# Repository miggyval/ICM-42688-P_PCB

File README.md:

This is a repository for the ICM-42688-P_PCB KiCAD project by Miguel Valencia

[Link to BOM](https://html-preview.github.io/?url=https://github.com/miggyval/ICM-42688-P_PCB/blob/main/bom/ibom.html)

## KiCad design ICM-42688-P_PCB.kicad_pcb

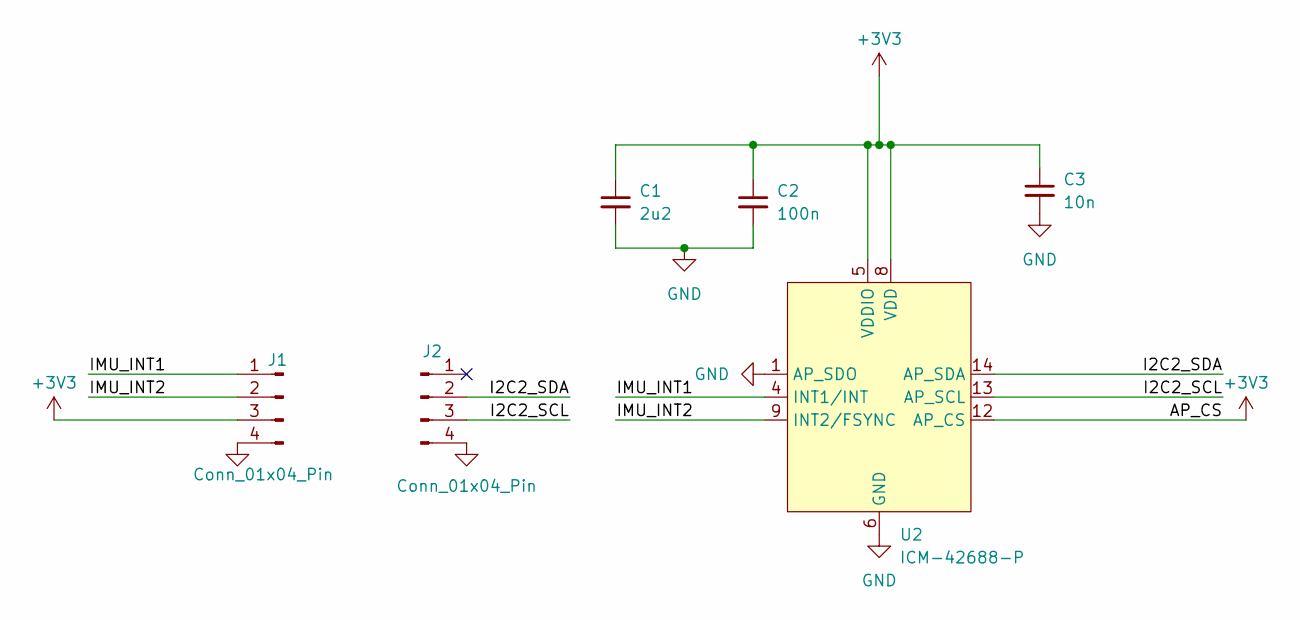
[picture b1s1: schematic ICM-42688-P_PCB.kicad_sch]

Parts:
C1: 2u2; C_1206_3216Metric_Pad1.33x1.80mm_HandSolder
C2: 100n; C_1206_3216Metric_Pad1.33x1.80mm_HandSolder
C3: 10n; C_1206_3216Metric_Pad1.33x1.80mm_HandSolder
J1, J2: Conn_01x04_Pin; PinHeader_1x04_P2.54mm_Vertical
U2: ICM-42688-P; LGA-14_3x2.5mm_P0.5mm_LayoutBorder3x4y_Keepout

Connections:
+3V3: C1.1, C2.1, C3.1, J1.3, U2.5 (VDDIO), U2.8 (VDD), U2.12 (AP_CS)
/I2C2_SCL: J2.3, U2.13 (AP_SCL)
/I2C2_SDA: J2.2, U2.14 (AP_SDA)
/IMU_INT1: J1.1, U2.4 (INT1/INT)
/IMU_INT2: J1.2, U2.9 (INT2/FSYNC)
GND: C1.2, C2.2, C3.2, J1.4, J2.4, U2.1 (AP_SDO), U2.6 (GND), U2.7 (RESV7), U2.11 (RESV11)

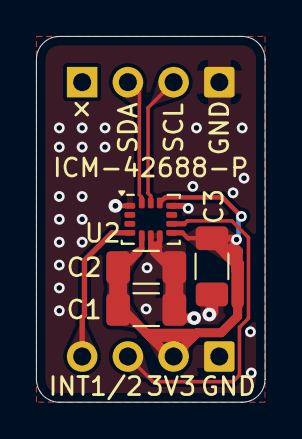
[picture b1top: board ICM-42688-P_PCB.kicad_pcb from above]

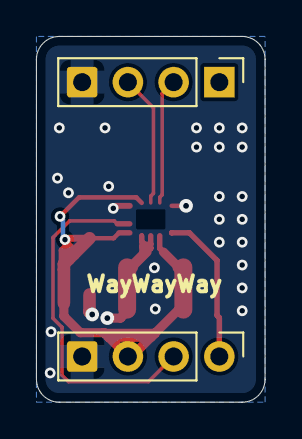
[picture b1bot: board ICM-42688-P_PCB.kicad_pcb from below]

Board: 2 copper layers, 12.7 x 20.3 mm, 6 parts (2 on the bottom side), 6 nets.

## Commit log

2024-09-30 First commit!
